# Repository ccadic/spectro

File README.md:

# spectroflurometer
Inspired but this article
https://create.arduino.cc/projecthub/dnhkng/the-pocket-lamp-illuminating-sars-cov-2-3a1d17?f=1#toc-electronics-3
Never tested

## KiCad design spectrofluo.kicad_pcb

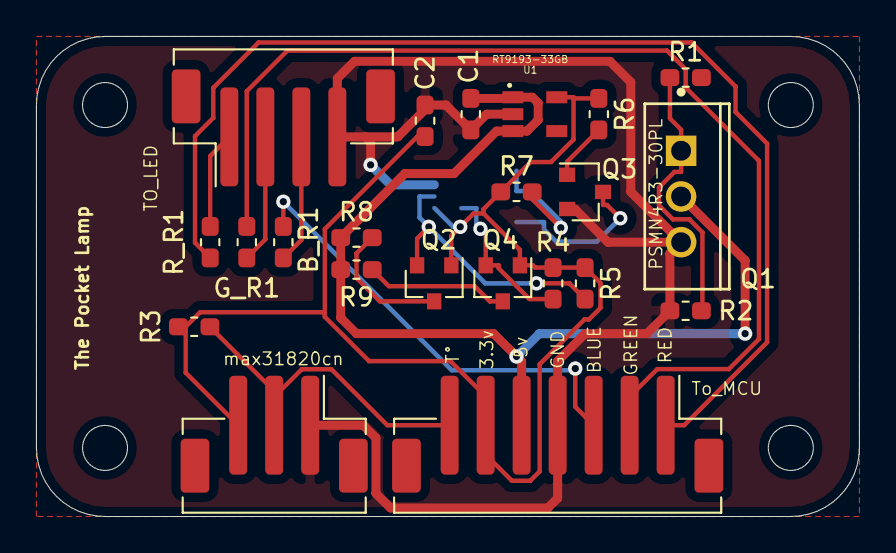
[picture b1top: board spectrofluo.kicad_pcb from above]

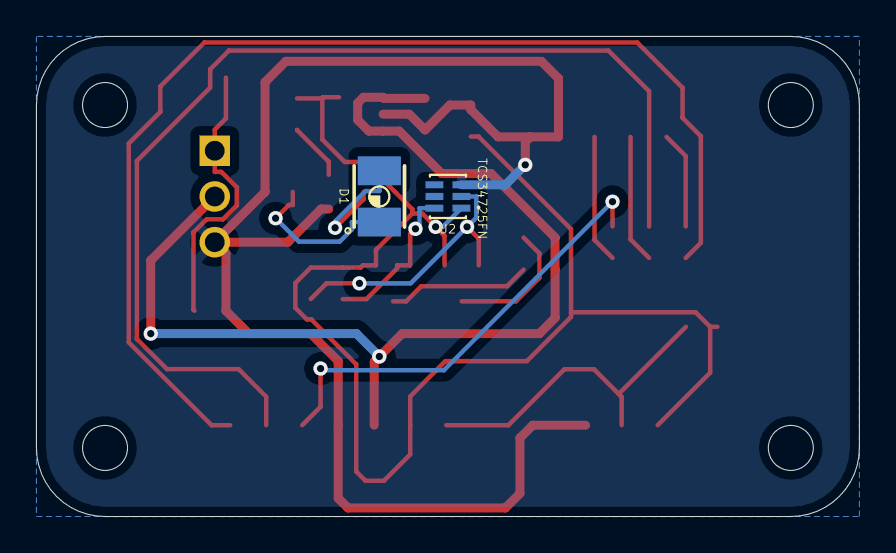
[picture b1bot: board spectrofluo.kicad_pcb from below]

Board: 2 copper layers, 45.7 x 26.7 mm, 28 parts (2 on the bottom side), 18 nets.

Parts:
B_R1: 100R; R_0603_1608Metric_Pad1.05x0.95mm_HandSolder
C1: 10uF; C_0603_1608Metric_Pad1.05x0.95mm_HandSolder
C2: 100nF; C_0603_1608Metric_Pad1.05x0.95mm_HandSolder
D1: LED_Small; VLMU3100
G_R1: 100R; R_0603_1608Metric_Pad1.05x0.95mm_HandSolder
H1, H2, H3, H4: MountingHole; MountingHole_2.5mm
J1: max31820cn; JST_PH_B3B-PH-SM4-TB_1x03-1MP_P2.00mm_Vertical
J2: To_MCU; JST_PH_B7B-PH-SM4-TB_1x07-1MP_P2.00mm_Vertical
J3: TO_LED; JST_PH_B4B-PH-SM4-TB_1x04-1MP_P2.00mm_Vertical
Q1: PSMN4R3-30PL
Q2, Q3, Q4: BSS138; SOT-23
R1: 220R; R_0603_1608Metric_Pad1.05x0.95mm_HandSolder
R2, R4, R5, R6, R8, R9: 10k; R_0603_1608Metric_Pad1.05x0.95mm_HandSolder
R3: 4.7k; R_0603_1608Metric_Pad1.05x0.95mm_HandSolder
R7: 6.8R; R_0603_1608Metric_Pad1.05x0.95mm_HandSolder
R_R1: 220R; R_0603_1608Metric_Pad1.05x0.95mm_HandSolder
U1: RT9193-33GB; RT9193
U2: TCS34725FN; TCS34725-6

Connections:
+3V3: C2.1, J1.3, J2.6, Q2.1, Q4.1, R3.2, R4.1, R5.1, R6.1, R7.1, U1.5, U2.1
+5V: C1.1, J2.5, Q1.2, R8.1, R9.1, U1.1, U1.3
/LED_EN: Q3.1, R6.2
/SCL_3V: Q2.2, R5.2, U2.2
/SCL_5V: Q2.3, R8.2
/SDA_3V: Q4.2, R4.2, U2.6
/SDA_5V: Q4.3, R9.2
/TEMP_Data: J1.2, J2.7, R3.1
GND: C1.2, C2.2, J1.1, J2.4, J3.4, Q1.3, Q3.2, R2.1, U1.2, U2.3
unnamed: B_R1.1, J3.3
unnamed: B_R1.2, J2.3
unnamed: D1.1, Q3.3
unnamed: D1.2, R7.2
unnamed: G_R1.1, J3.2
unnamed: G_R1.2, J2.2
unnamed: J2.1, R_R1.2
unnamed: J3.1, R_R1.1
unnamed: Q1.1, R1.1, R2.2
